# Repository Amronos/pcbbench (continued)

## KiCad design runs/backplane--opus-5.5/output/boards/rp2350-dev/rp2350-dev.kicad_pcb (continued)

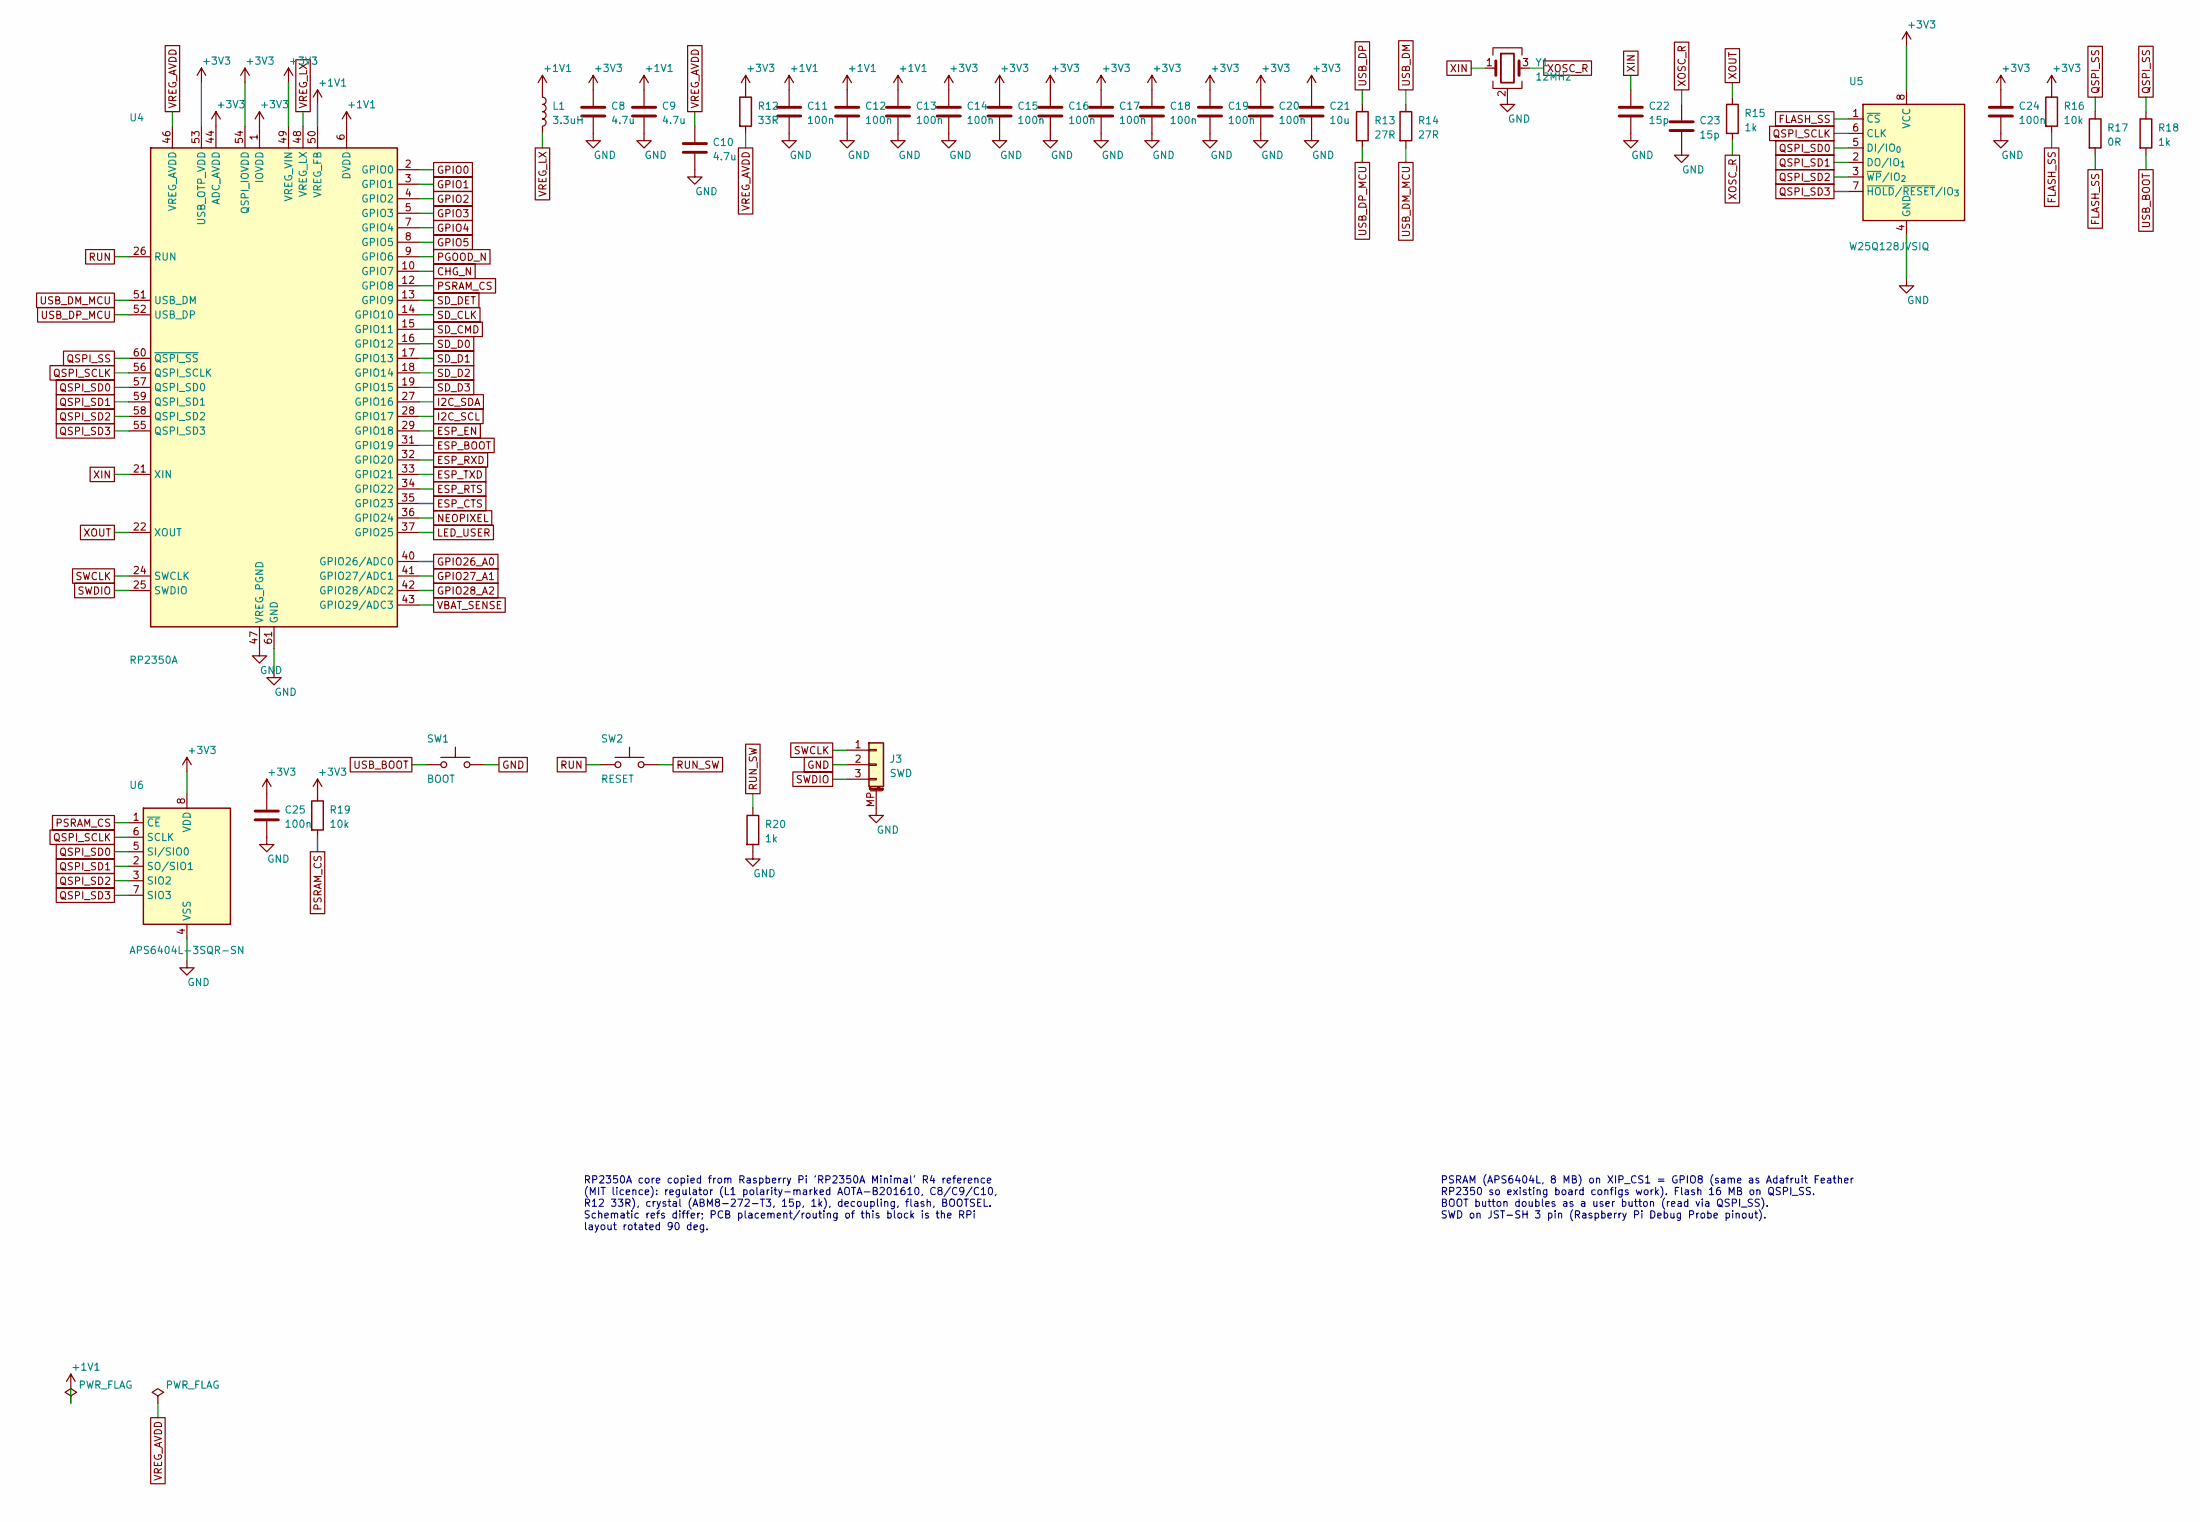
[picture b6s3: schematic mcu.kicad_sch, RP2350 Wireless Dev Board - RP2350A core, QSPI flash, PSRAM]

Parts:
C8, C9: 4.7u; C_0402_RPi_Wide; MPN CL05A475MP5NRNC; LCSC C23733
C10: 4.7u; C_0402_RPi; MPN CL05A475MP5NRNC; LCSC C23733
C11, C12, C13, C14, C15, C16, C17, C18, C19, C20, C24: 100n; C_0402_RPi; MPN CL05B104KO5NNNC; LCSC C1525
C21: 10u; C_0603_1608Metric; MPN CL10A106MA8NRNC; LCSC C96446
C22, C23: 15p; C_0402_RPi; MPN 0402CG150J500NT; LCSC C1548
C25: 100n; C_0402_1005Metric; MPN CL05B104KO5NNNC; LCSC C1525
J3: SWD; JST_SH_SM03B-SRSS-TB_1x03-1MP_P1.00mm_Horizontal; MPN SM03B-SRSS-TB(LF)(SN); LCSC C160403
L1: 3.3uH; L_Abracon_AOTA-B201610; MPN AOTA-B201610S3R3-101-T; LCSC C42411119
R12: 33R; R_0402_RPi; MPN 0402WGF330JTCE; LCSC C25105
R13, R14: 27R; R_0402_RPi; MPN 0402WGF270JTCE; LCSC C25100
R15, R18: 1k; R_0402_RPi; MPN 0402WGF1001TCE; LCSC C11702
R16: 10k; R_0402_RPi; MPN 0402WGF1002TCE; LCSC C25744
R17: 0R; R_0402_RPi; MPN 0402WGF0000TCE; LCSC C17168
R19: 10k; R_0402_1005Metric; MPN 0402WGF1002TCE; LCSC C25744
R20: 1k; R_0402_1005Metric; MPN 0402WGF1001TCE; LCSC C11702
SW1: BOOT; SW_SPST_PTS810; MPN PTS810 SJM 250 SMTR LFS; LCSC C116501
SW2: RESET; SW_SPST_PTS810; MPN PTS810 SJM 250 SMTR LFS; LCSC C116501
U4: RP2350A; RP2350A_QFN60_RPi; MPN RP2350A; LCSC C42411118
U5: W25Q128JVSIQ; SOIC-8_5.3mm_RPi; MPN W25Q128JVSIQ; LCSC C97521
U6: APS6404L-3SQR-SN; SOIC-8_3.9x4.9mm_P1.27mm; MPN APS6404L-3SQR-SN; LCSC C5333729
Y1: 12MHz; Crystal_3225_RPi; MPN ABM8-272-T3; LCSC C20625731

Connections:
+1V1: C9.1, C11.1, C12.1, C13.1, L1.1, U4.6 (DVDD), U4.23 (DVDD), U4.39 (DVDD), U4.50 (VREG_FB)
+3V3: C8.1, C14.1, C15.1, C16.1, C17.1, C18.1, C19.1, C20.1, C21.1, C24.1, C25.1, R12.1, R16.1, R19.1, U4.1 (IOVDD), U4.11 (IOVDD), U4.20 (IOVDD), U4.30 (IOVDD), U4.38 (IOVDD), U4.44 (ADC_AVDD), U4.45 (IOVDD), U4.49 (VREG_VIN), U4.53 (USB_OTP_VDD), U4.54 (QSPI_IOVDD), U5.8 (VCC), U6.8 (VDD); also elsewhere on the board
CHG_N: U4.10 (GPIO7); also elsewhere on the board
ESP_BOOT: U4.31 (GPIO19); also elsewhere on the board
ESP_CTS: U4.35 (GPIO23); also elsewhere on the board
ESP_EN: U4.29 (GPIO18); also elsewhere on the board
ESP_RTS: U4.34 (GPIO22); also elsewhere on the board
ESP_RXD: U4.32 (GPIO20); also elsewhere on the board
ESP_TXD: U4.33 (GPIO21); also elsewhere on the board
FLASH_SS: R16.2, R17.2, U5.1 (~CS)
GND: C8.2, C9.2, C10.2, C11.2, C12.2, C13.2, C14.2, C15.2, C16.2, C17.2, C18.2, C19.2, C20.2, C21.2, C22.2, C23.2, C24.2, C25.2, J3.2, J3.MP (MountPin), R20.2, SW1.2, U4.47 (VREG_PGND), U4.61 (GND), U5.4 (GND), U6.4 (VSS), Y1.2, Y1.4; also elsewhere on the board
GPIO0: U4.2 (GPIO0); also elsewhere on the board
GPIO1: U4.3 (GPIO1); also elsewhere on the board
GPIO2: U4.4 (GPIO2); also elsewhere on the board
GPIO3: U4.5 (GPIO3); also elsewhere on the board
GPIO4: U4.7 (GPIO4); also elsewhere on the board
GPIO5: U4.8 (GPIO5); also elsewhere on the board
GPIO26_A0: U4.40 (GPIO26_ADC0); also elsewhere on the board
GPIO27_A1: U4.41 (GPIO27_ADC1); also elsewhere on the board
GPIO28_A2: U4.42 (GPIO28_ADC2); also elsewhere on the board
I2C_SCL: U4.28 (GPIO17); also elsewhere on the board
I2C_SDA: U4.27 (GPIO16); also elsewhere on the board
LED_USER: U4.37 (GPIO25); also elsewhere on the board
NEOPIXEL: U4.36 (GPIO24); also elsewhere on the board
PGOOD_N: U4.9 (GPIO6); also elsewhere on the board
PSRAM_CS: R19.2, U4.12 (GPIO8), U6.1 (~CE)
QSPI_SCLK: U4.56 (QSPI_SCLK), U5.6 (CLK), U6.6 (SCLK)
QSPI_SD0: U4.57 (QSPI_SD0), U5.5 (DI_IO0), U6.5 (SI/SIO0)
QSPI_SD1: U4.59 (QSPI_SD1), U5.2 (DO_IO1), U6.2 (SO/SIO1)
QSPI_SD2: U4.58 (QSPI_SD2), U5.3 (~WP_IO2), U6.3 (SIO2)
QSPI_SD3: U4.55 (QSPI_SD3), U5.7 (~HOLD_IO3), U6.7 (SIO3)
QSPI_SS: R17.1, R18.1, U4.60 (QSPI_~SS)
RUN: SW2.1, U4.26 (RUN); also elsewhere on the board
RUN_SW: R20.1, SW2.2
SD_CLK: U4.14 (GPIO10); also elsewhere on the board
SD_CMD: U4.15 (GPIO11); also elsewhere on the board
SD_D0: U4.16 (GPIO12); also elsewhere on the board
SD_D1: U4.17 (GPIO13); also elsewhere on the board
SD_D2: U4.18 (GPIO14); also elsewhere on the board
SD_D3: U4.19 (GPIO15); also elsewhere on the board
SD_DET: U4.13 (GPIO9); also elsewhere on the board
SWCLK: J3.1, U4.24 (SWCLK)
SWDIO: J3.3, U4.25 (SWDIO)
USB_BOOT: R18.2, SW1.1
USB_DM: R14.1; also elsewhere on the board
USB_DM_MCU: R14.2, U4.51 (USB_DM)
USB_DP: R13.1; also elsewhere on the board
USB_DP_MCU: R13.2, U4.52 (USB_DP)
VBAT_SENSE: U4.43 (GPIO29_ADC3); also elsewhere on the board
VREG_AVDD: C10.1, R12.2, U4.46 (VREG_AVDD)
VREG_LX: L1.2, U4.48 (VREG_LX)
XIN: C22.1, U4.21 (XIN), Y1.1
XOSC_R: C23.1, R15.2, Y1.3
XOUT: R15.1, U4.22 (XOUT)

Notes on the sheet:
RP2350A core copied from Raspberry Pi 'RP2350A Minimal' R4 reference (MIT licence): regulator (L1 polarity-marked AOTA-B201610, C8/C9/C10, R12 33R), crystal (ABM8-272-T3, 15p, 1k), decoupling, flash, BOOTSEL. Schematic refs differ; PCB placement/routing of this block is the RPi layout rotated 90 de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
PSRAM (APS6404L, 8 MB) on XIP_CS1 = GPIO8 (same as Adafruit Feather RP2350 so existing board configs work). Flash 16 MB on QSPI_SS. BOOT button doubles as a user button (read via QSPI_SS). SWD on JST-SH 3 pin (Raspberry Pi Debug Probe pinout).

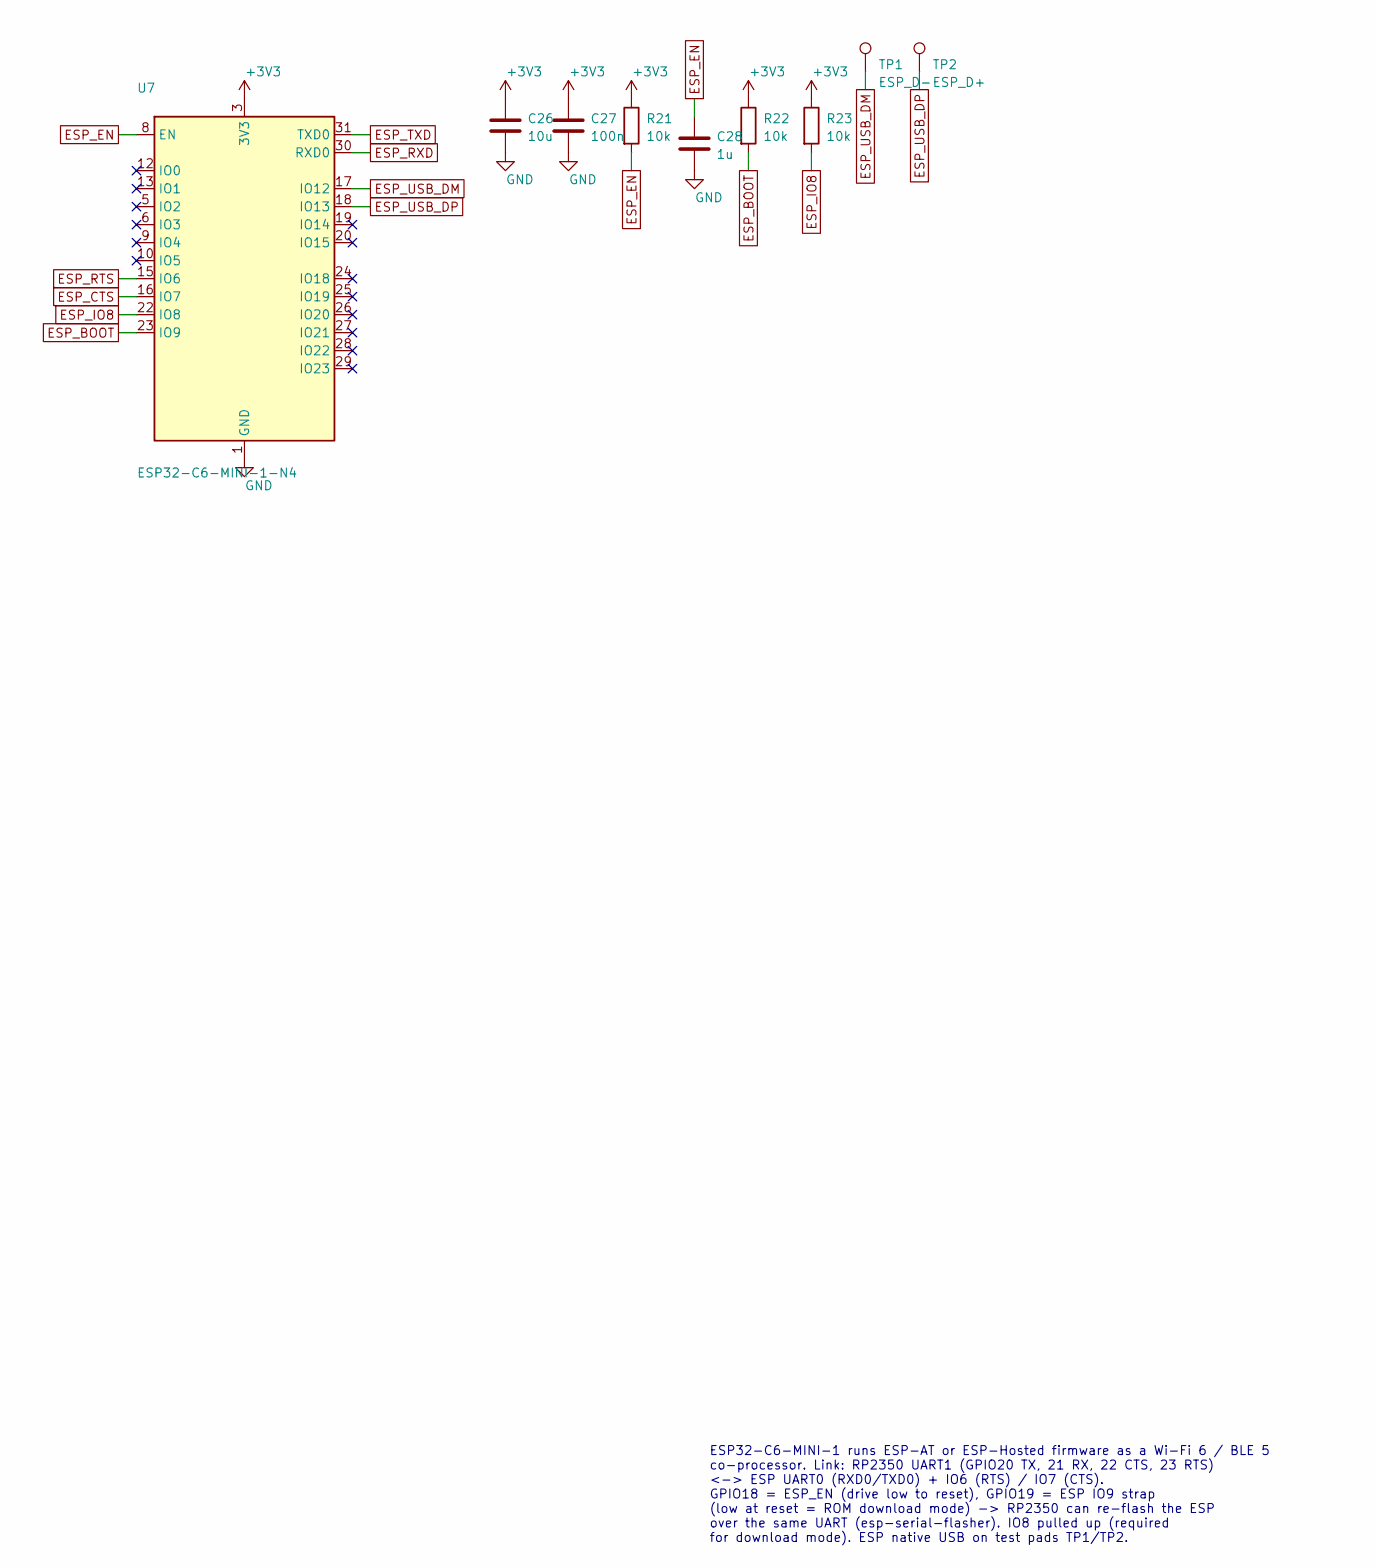
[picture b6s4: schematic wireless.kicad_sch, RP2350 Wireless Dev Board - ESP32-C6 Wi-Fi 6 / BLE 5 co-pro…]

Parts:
C26: 10u; C_0603_1608Metric; MPN CL10A106MA8NRNC; LCSC C96446
C27: 100n; C_0402_1005Metric; MPN CL05B104KO5NNNC; LCSC C1525
C28: 1u; C_0402_1005Metric; MPN CL05A105KA5NQNC; LCSC C52923
R21, R22, R23: 10k; R_0402_1005Metric; MPN 0402WGF1002TCE; LCSC C25744
TP1: ESP_D-; TestPoint_Pad_D1.0mm
TP2: ESP_D+; TestPoint_Pad_D1.0mm
U7: ESP32-C6-MINI-1-N4; ESP32-C6-MINI-1_BoardEdge; MPN ESP32-C6-MINI-1-N4; LCSC C5736265

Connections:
+3V3: C26.1, C27.1, R21.1, R22.1, R23.1, U7.3 (3V3); also elsewhere on the board
ESP_BOOT: R22.2, U7.23 (IO9); also elsewhere on the board
ESP_CTS: U7.16 (IO7); also elsewhere on the board
ESP_EN: C28.1, R21.2, U7.8 (EN); also elsewhere on the board
ESP_IO8: R23.2, U7.22 (IO8)
ESP_RTS: U7.15 (IO6); also elsewhere on the board
ESP_RXD: U7.30 (RXD0); also elsewhere on the board
ESP_TXD: U7.31 (TXD0); also elsewhere on the board
ESP_USB_DM: TP1.1, U7.17 (IO12)
ESP_USB_DP: TP2.1, U7.18 (IO13)
GND: C26.2, C27.2, C28.2, U7.1 (GND), U7.2 (GND), U7.11 (GND), U7.14 (GND), U7.36 (GND), U7.37 (GND), U7.38 (GND), U7.39 (GND), U7.40 (GND), U7.41 (GND), U7.42 (GND), U7.43 (GND), U7.44 (GND), U7.45 (GND), U7.46 (GND), U7.47 (GND), U7.48 (GND), U7.49 (GND), U7.50 (GND), U7.51 (GND), U7.52 (GND), U7.53 (GND); also elsewhere on the board

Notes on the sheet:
ESP32-C6-MINI-1 runs ESP-AT or ESP-Hosted firmware as a Wi-Fi 6 / BLE 5 co-processor. Link: RP2350 UART1 (GPIO20 TX, 21 RX, 22 CTS, 23 RTS) <-> ESP UART0 (RXD0/TXD0) + IO6 (RTS) / IO7 (CTS). GPIO18 = ESP_EN (drive low to reset), GPIO19 = ESP IO9 strap (low at reset = ROM download mode) -> RP2350 ca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

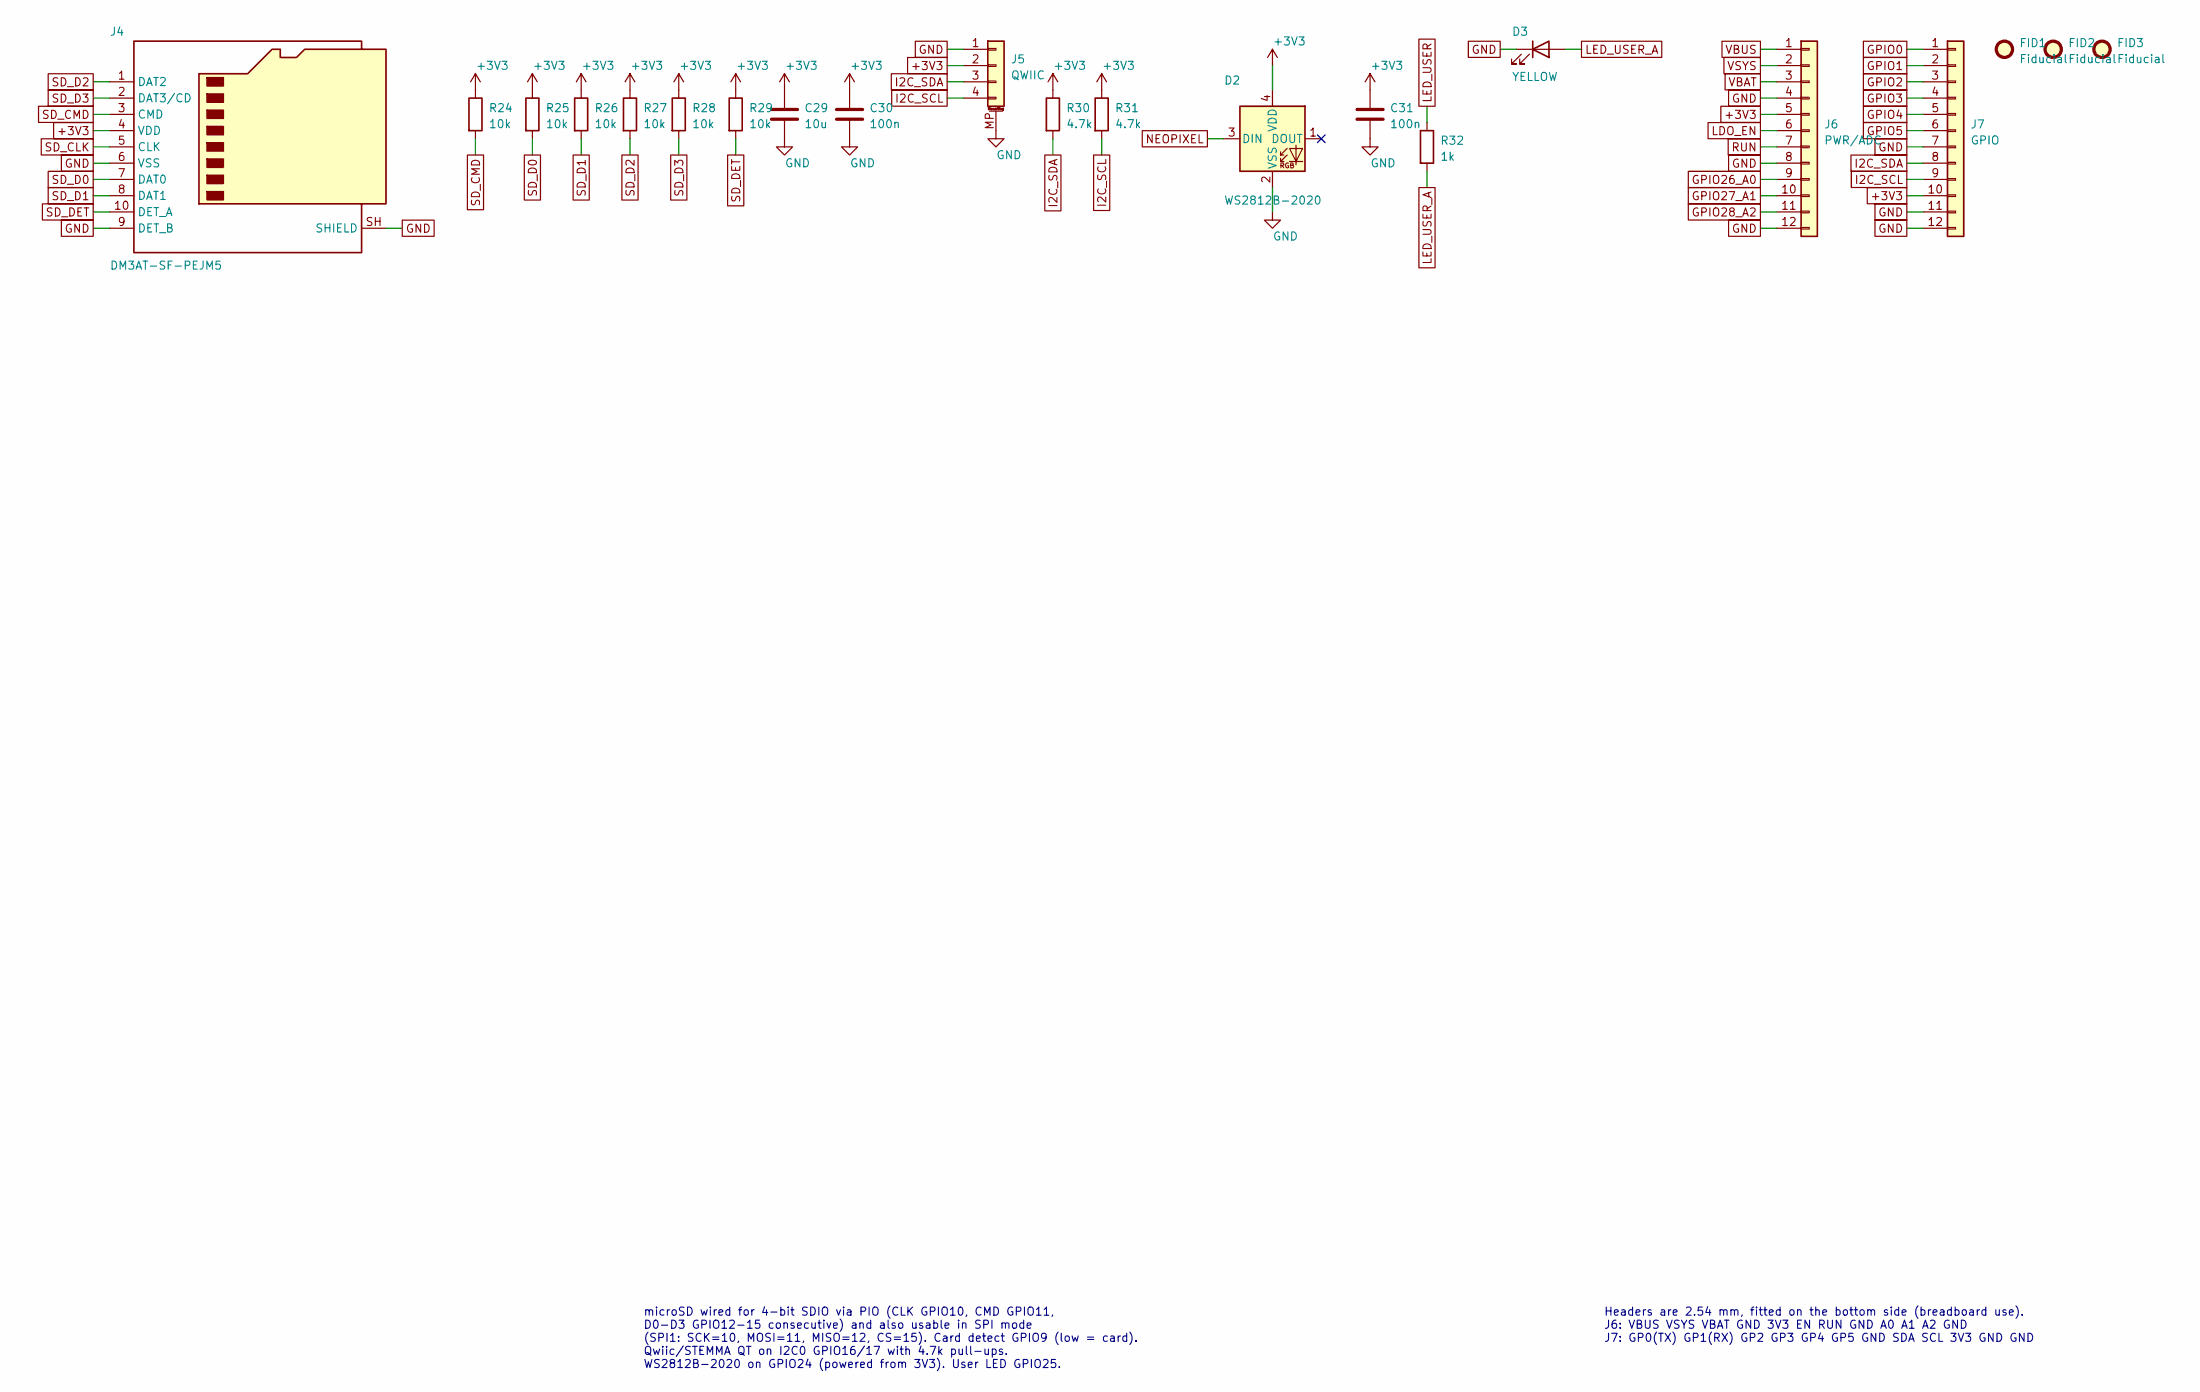
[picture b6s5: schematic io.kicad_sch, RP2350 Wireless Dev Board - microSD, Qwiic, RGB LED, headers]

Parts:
C29: 10u; C_0603_1608Metric; MPN CL10A106MA8NRNC; LCSC C96446
C30, C31: 100n; C_0402_1005Metric; MPN CL05B104KO5NNNC; LCSC C1525
D2: WS2812B-2020; LED_WS2812B-2020_PLCC4_2.0x2.0mm; MPN WS2812B-2020-V6; LCSC C52917434
D3: YELLOW; LED_0603_1608Metric; MPN NCD0603Y2; LCSC C89811
FID1, FID2, FID3: Fiducial; Fiducial_1mm_Mask2mm
J4: DM3AT-SF-PEJM5; microSD_HC_Hirose_DM3AT-SF-PEJM5; MPN DM3AT-SF-PEJM5; LCSC C114218
J5: QWIIC; JST_SH_SM04B-SRSS-TB_1x04-1MP_P1.00mm_Horizontal; MPN SM04B-SRSS-TB(LF)(SN); LCSC C160404
J6: PWR/ADC; PinHeader_1x12_P2.54mm_Vertical; MPN PZ254V-11-12P; LCSC C2840012
J7: GPIO; PinHeader_1x12_P2.54mm_Vertical; MPN PZ254V-11-12P; LCSC C2840012
R24, R25, R26, R27, R28, R29: 10k; R_0402_1005Metric; MPN 0402WGF1002TCE; LCSC C25744
R30, R31: 4.7k; R_0402_1005Metric; MPN 0402WGF4701TCE; LCSC C25900
R32: 1k; R_0402_1005Metric; MPN 0402WGF1001TCE; LCSC C11702

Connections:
+3V3: C29.1, C30.1, C31.1, D2.4 (VDD), J4.4 (VDD), J5.2, J6.5, J7.10, R24.1, R25.1, R26.1, R27.1, R28.1, R29.1, R30.1, R31.1; also elsewhere on the board
GND: C29.2, C30.2, C31.2, D2.2 (VSS), D3.1 (K), J4.6 (VSS), J4.9 (DET_B), J4.SH (SHIELD), J5.1, J5.MP (MountPin), J6.4, J6.8, J6.12, J7.7, J7.11, J7.12; also elsewhere on the board
GPIO0: J7.1; also elsewhere on the board
GPIO1: J7.2; also elsewhere on the board
GPIO2: J7.3; also elsewhere on the board
GPIO3: J7.4; also elsewhere on the board
GPIO4: J7.5; also elsewhere on the board
GPIO5: J7.6; also elsewhere on the board
GPIO26_A0: J6.9; also elsewhere on the board
GPIO27_A1: J6.10; also elsewhere on the board
GPIO28_A2: J6.11; also elsewhere on the board
I2C_SCL: J5.4, J7.9, R31.2; also elsewhere on the board
I2C_SDA: J5.3, J7.8, R30.2; also elsewhere on the board
LDO_EN: J6.6; also elsewhere on the board
LED_USER: R32.1; also elsewhere on the board
LED_USER_A: D3.2 (A), R32.2
NEOPIXEL: D2.3 (DIN); also elsewhere on the board
RUN: J6.7; also elsewhere on the board
SD_CLK: J4.5 (CLK); also elsewhere on the board
SD_CMD: J4.3 (CMD), R24.2; also elsewhere on the board
SD_D0: J4.7 (DAT0), R25.2; also elsewhere on the board
SD_D1: J4.8 (DAT1), R26.2; also elsewhere on the board
SD_D2: J4.1 (DAT2), R27.2; also elsewhere on the board
SD_D3: J4.2 (DAT3/CD), R28.2; also elsewhere on the board
SD_DET: J4.10 (DET_A), R29.2; also elsewhere on the board
VBAT: J6.3; also elsewhere on the board
VBUS: J6.1; also elsewhere on the board
VSYS: J6.2; also elsewhere on the board

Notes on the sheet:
microSD wired for 4-bit SDIO via PIO (CLK GPIO10, CMD GPIO11, D0-D3 GPIO12-15 consecutive) and also usable in SPI mode (SPI1: SCK=10, MOSI=11, MISO=12, CS=15). Card detect GPIO9 (low = card). Qwiic/STEMMA QT on I2C0 GPIO16/17 with 4.7k pull-ups. WS2812B-2020 on GPIO24 (powered from 3V3). User LED G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
Headers are 2.54 mm, fitted on the bottom side (breadboard use). J6: VBUS VSYS VBAT GND 3V3 EN RUN GND A0 A1 A2 GND J7: GP0(TX) GP1(RX) GP2 GP3 GP4 GP5 GND SDA SCL 3V3 GND GND

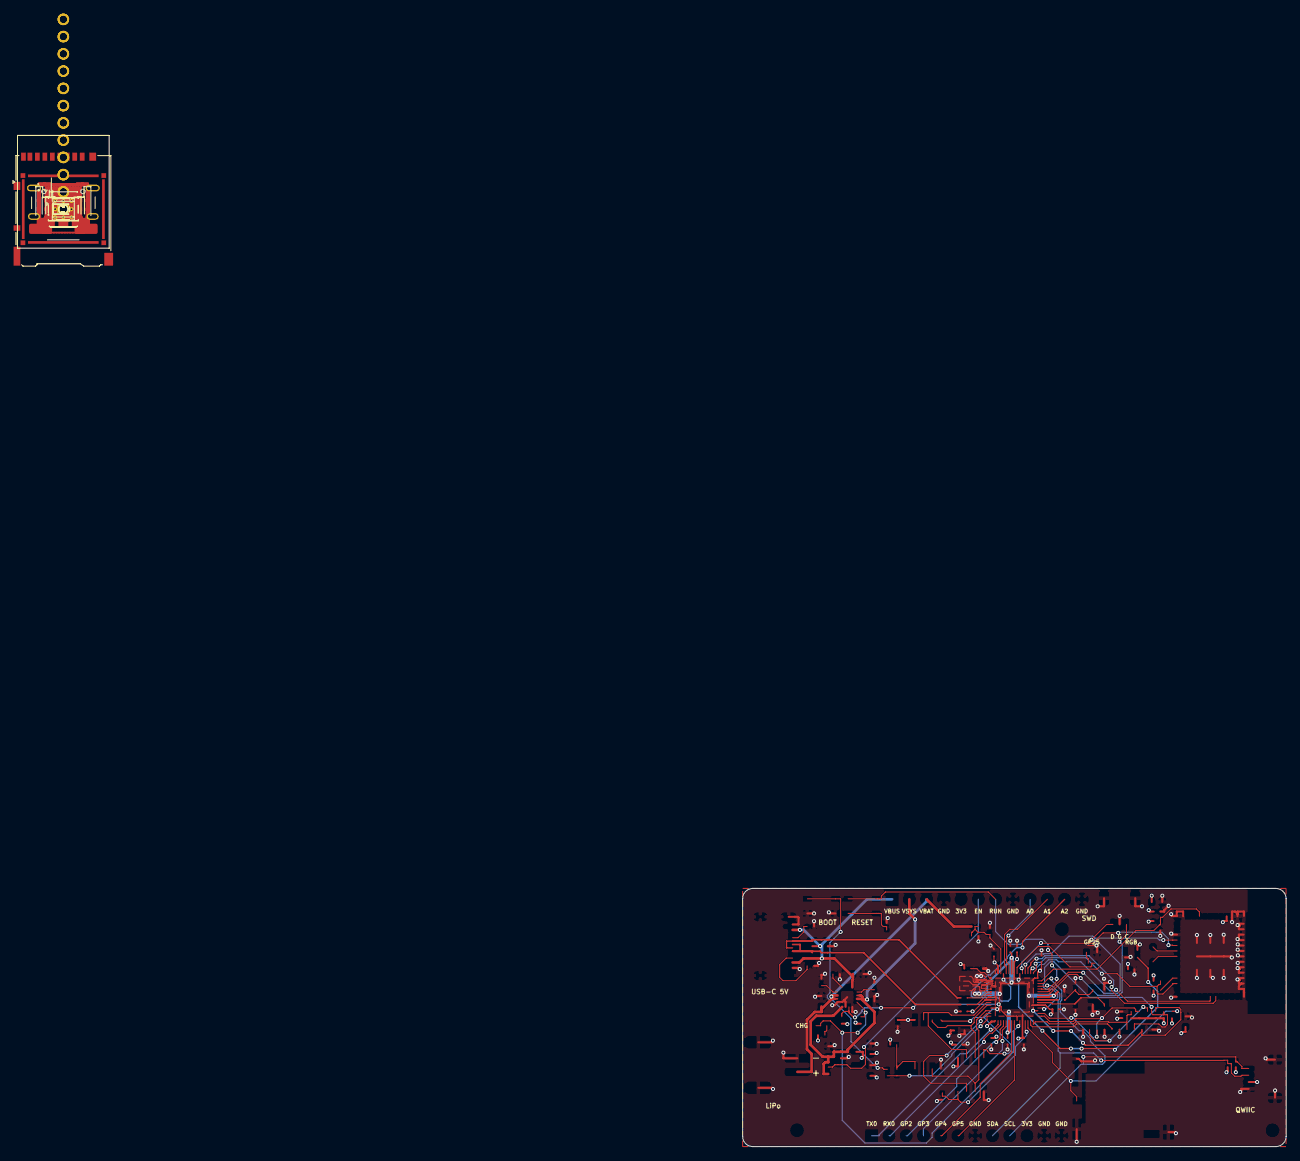
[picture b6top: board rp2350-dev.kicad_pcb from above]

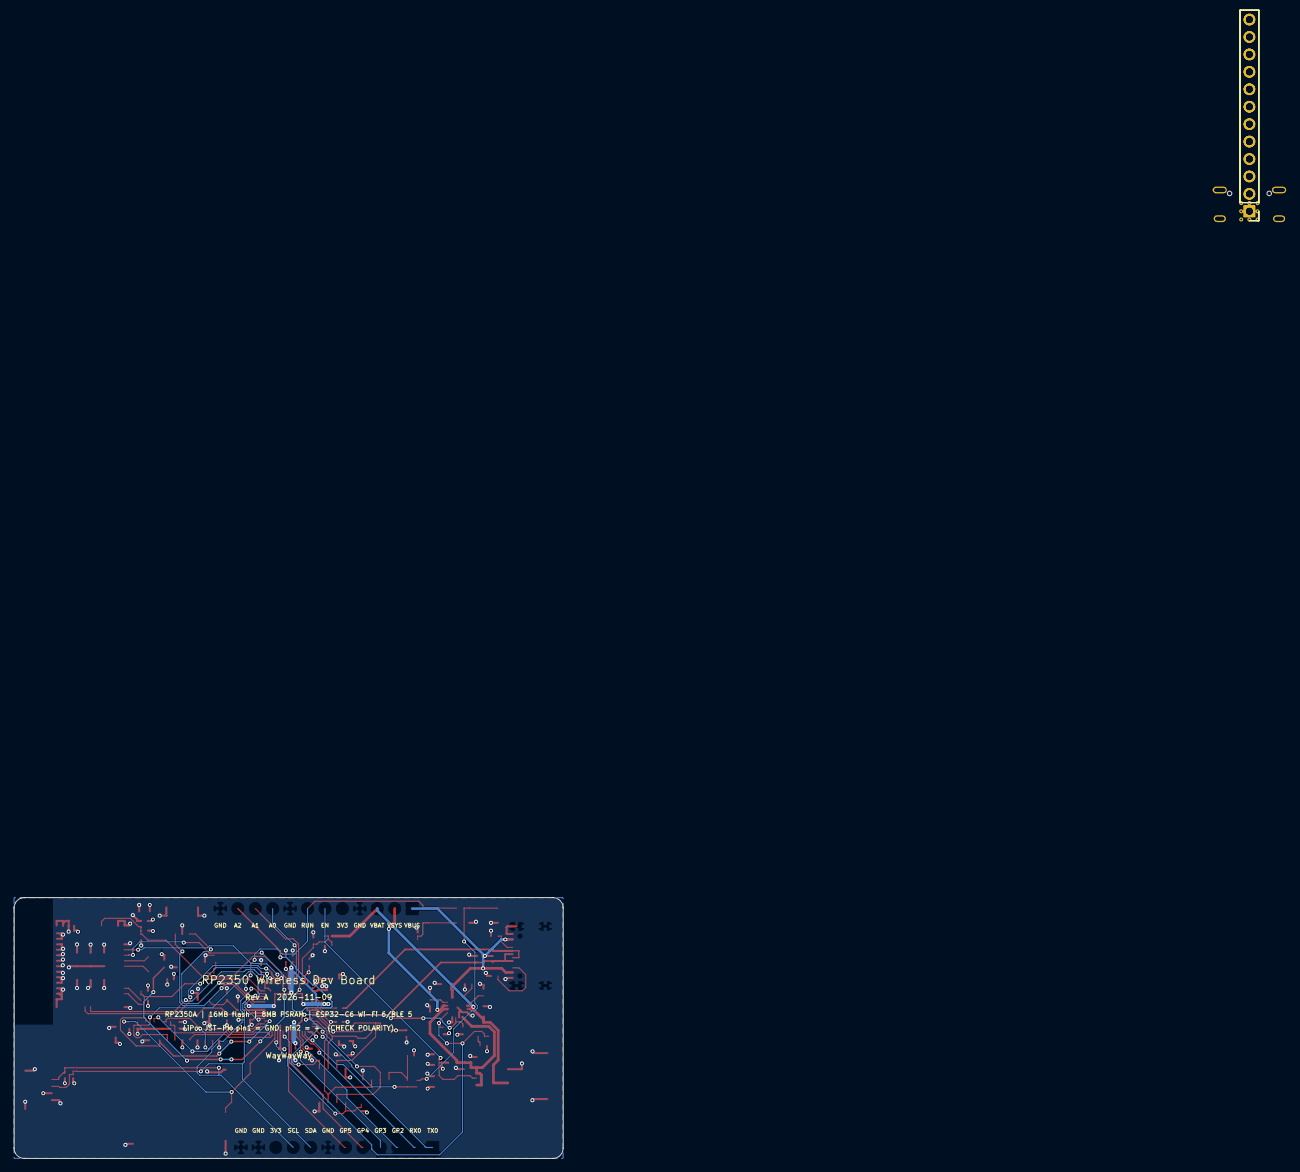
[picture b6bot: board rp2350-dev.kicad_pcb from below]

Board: 4 copper layers, 80.0 x 38.0 mm, 89 parts (2 on the bottom side), 68 nets.

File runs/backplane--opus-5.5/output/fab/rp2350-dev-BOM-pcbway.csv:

Item #,Designator,Qty,Manufacturer,Mfg Part #,Description / Value,Package/Footprint,Type,Side,LCSC Part #,Your Instructions / Notes
1,C1,1,Samsung Electro-Mechanics,CL10A475KA8NQNC,4.7u - 4.7uF 25V X5R 0603,0603,SMD,top,C69335,
2,"C2,C3,C5,C6,C7,C21,C26,C29",8,Samsung Electro-Mechanics,CL10A106MA8NRNC,10u - 10uF 25V X5R 0603,0603,SMD,top,C96446,
3,"C4,C11,C12,C13,C14,C15,C16,C17,C18,C19,C20,C24,C25,C27,C30,C31",16,Samsung Electro-Mechanics,CL05B104KO5NNNC,100n - 100nF 16V X7R 0402,0402,SMD,top,C1525,
4,"C8,C9,C10",3,Samsung Electro-Mechanics,CL05A475MP5NRNC,4.7u - 4.7uF 10V X5R 0402,0402,SMD,top,C23733,
5,"C22,C23",2,FH (Fenghua),0402CG150J500NT,15p - 15pF 50V C0G 0402,0402,SMD,top,C1548,
6,C28,1,Samsung Electro-Mechanics,CL05A105KA5NQNC,1u - 1uF 25V X5R 0402,0402,SMD,top,C52923,
7,D1,1,Hubei KENTO Elec,KT-0603R,RED - LED red 0603 (charging),LED_0603_1608Metric,SMD,top,C2286,Polarity: cathode = pin 1
8,D2,1,Worldsemi,WS2812B-2020-V6,WS2812B-2020 - Addressable RGB LED 2.0x2.0mm,LED_WS2812B-2020_PLCC4_2.0x2.0mm,SMD,top,C52917434,
9,D3,1,Foshan NationStar,NCD0603Y2,"YELLOW - LED yellow 0603 (user, GPIO25)",LED_0603_1608Metric,SMD,top,C89811,Polarity: cathode = pin 1
10,J1,1,GCT,USB4105-GF-A,"USB4105-GF-A - USB Type-C receptacle, USB 2.0, 16P, SMD + THT shell",USB_C_Receptacle_GCT_USB4105-xx-A_16P_TopMnt_Horizontal,SMD,top,C3020560,
11,J2,1,JST,S2B-PH-SM4-TB(LF)(SN),"BATT - JST PH 2-pin right-angle SMD, Li-Po battery (pin1 = GND, pin2 = +)",JST_PH_S2B-PH-SM4-TB_1x02-1MP_P2.00mm_Horizontal,SMD,top,C295747,
12,J3,1,JST,SM03B-SRSS-TB(LF)(SN),"SWD - JST SH 3-pin, Raspberry Pi Debug Connector pinout (SWCLK/GND/SWDIO)",JST_SH_SM03B-SRSS-TB_1x03-1MP_P1.00mm_Horizontal,SMD,top,C160403,
13,J4,1,Hirose,DM3AT-SF-PEJM5,DM3AT-SF-PEJM5 - microSD push-push socket with card detect,microSD_HC_Hirose_DM3AT-SF-PEJM5,SMD,top,C114218,
14,J5,1,JST,SM04B-SRSS-TB(LF)(SN),QWIIC - JST SH 4-pin (Qwiic / STEMMA QT),JST_SH_SM04B-SRSS-TB_1x04-1MP_P1.00mm_Horizontal,SMD,top,C160404,
15,J6,1,XFCN,PZ254V-11-12P,"PWR/ADC - 1x12 2.54mm male header, THT (fit on bottom side)",PinHeader_1x12_P2.54mm_Vertical,THT,bottom,C2840012,"THT: insert from BOTTOM side (plastic body under the board), solder on top side"
16,J7,1,XFCN,PZ254V-11-12P,"GPIO - 1x12 2.54mm male header, THT (fit on bottom side)",PinHeader_1x12_P2.54mm_Vertical,THT,bottom,C2840012,"THT: insert from BOTTOM side (plastic body under the board), solder on top side"
17,L1,1,Abracon,AOTA-B201610S3R3-101-T,"3.3uH - 3.3uH 2016 polarity-marked inductor (RP2350 VREG, orientation critical)",L_Abracon_AOTA-B201610,SMD,top,C42411119,Polarity-marked inductor: dot must match footprint pin 1 marking (RP2350 VREG requirement)
18,"R1,R2",2,UNI-ROYAL,0402WGF5101TCE,5.1k - Thick-film resistor 5.1k 1% 62.5mW 0402,0402,SMD,top,C25905,
19,"R3,R16,R19,R21,R22,R23,R24,R25,R26,R27,R28,R29",12,UNI-ROYAL,0402WGF1002TCE,10k - Thick-film resistor 10k 1% 62.5mW 0402,0402,SMD,top,C25744,
20,R4,1,UNI-ROYAL,0402WGF1501TCE,1.5k - Thick-film resistor 1.5k 1% 62.5mW 0402,0402,SMD,top,C25867,
21,R5,1,UNI-ROYAL,0402WGF2001TCE,2k - Thick-film resistor 2k 1% 62.5mW 0402,0402,SMD,top,C4109,
22,"R6,R7,R10,R11",4,UNI-ROYAL,0402WGF1003TCE,100k - Thick-film resistor 100k 1% 62.5mW 0402,0402,SMD,top,C25741,
23,"R8,R15,R18,R20,R32",5,UNI-ROYAL,0402WGF1001TCE,1k - Thick-film resistor 1k 1% 62.5mW 0402,0402,SMD,top,C11702,
24,R9,1,UNI-ROYAL,0402WGF2003TCE,200k - Thick-film resistor 200k 1% 62.5mW 0402,0402,SMD,top,C25764,
25,R12,1,UNI-ROYAL,0402WGF330JTCE,33R - Thick-film resistor 33R 1% 62.5mW 0402,0402,SMD,top,C25105,
26,"R13,R14",2,UNI-ROYAL,0402WGF270JTCE,27R - Thick-film resistor 27R 1% 62.5mW 0402,0402,SMD,top,C25100,
27,R17,1,UNI-ROYAL,0402WGF0000TCE,0R - Thick-film resistor 0R 1% 62.5mW 0402,0402,SMD,top,C17168,
28,"R30,R31",2,UNI-ROYAL,0402WGF4701TCE,4.7k - Thick-film resistor 4.7k 1% 62.5mW 0402,0402,SMD,top,C25900,
29,SW1,1,C&K,PTS810 SJM 250 SMTR LFS,BOOT - Tactile switch 4.2x3.2mm SMD (BOOTSEL),SW_SPST_PTS810,SMD,top,C116501,
30,SW2,1,C&K,PTS810 SJM 250 SMTR LFS,RESET - Tactile switch 4.2x3.2mm SMD (RESET),SW_SPST_PTS810,SMD,top,C116501,
31,U1,1,STMicroelectronics,USBLC6-2SC6,"USBLC6-2SC6 - USB 2.0 ESD protection, SOT-23-6",SOT-23-6,SMD,top,C7519,
32,U2,1,Texas Instruments,BQ24074RGTR,"BQ24074RGTR - 1.5A single-cell Li-ion charger with DPPM power-path, VQFN-16",VQFN-16-1EP_3x3mm_P0.5mm_EP1.6x1.6mm,SMD,top,C54313,
33,U3,1,Texas Instruments,TLV75733PDBVR,"TLV75733PDBVR - 1A 3.3V LDO, SOT-23-5",SOT-23-5,SMD,top,C485517,
34,U4,1,Raspberry Pi,RP2350A,"RP2350A - RP2350A dual Cortex-M33/Hazard3 MCU, QFN-60 7x7",RP2350A_QFN60_RPi,SMD,top,C42411118,
35,U5,1,Winbond,W25Q128JVSIQ,"W25Q128JVSIQ - 128Mbit (16MB) QSPI NOR flash, SOIC-8 208mil",SOIC-8_5.3mm_RPi,SMD,top,C97521,
36,U6,1,AP Memory,APS6404L-3SQR-SN,"APS6404L-3SQR-SN - 64Mbit (8MB) QSPI PSRAM 3.3V, SOP-8",SOIC-8_3.9x4.9mm_P1.27mm,SMD,top,C5333729,
37,U7,1,Espressif,ESP32-C6-MINI-1-N4,"ESP32-C6-MINI-1-N4 - Wi-Fi 6 / BLE 5 / 802.15.4 module, PCB antenna, 4MB flash",ESP32-C6-MINI-1_BoardEdge,SMD,top,C5736265,Module: no copper/parts under antenna; antenna overhangs board edge region
38,Y1,1,Abracon,ABM8-272-T3,12MHz - 12MHz crystal 10pF 3.2x2.5 (RPi recommended),Crystal_3225_RPi,SMD,top,C20625731,
